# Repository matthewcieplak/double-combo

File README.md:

# AmpSim

## Author

Extralife Instruments

## Description

Amp sim module for Eurorack using Daisy Patch.

## Programming setup: 

Plug the daisy patch into the PC using USB.

Download and install Zadig. Run it to install the USB driver.

Build and program the device from source in VS code or use the daisy web uploader.

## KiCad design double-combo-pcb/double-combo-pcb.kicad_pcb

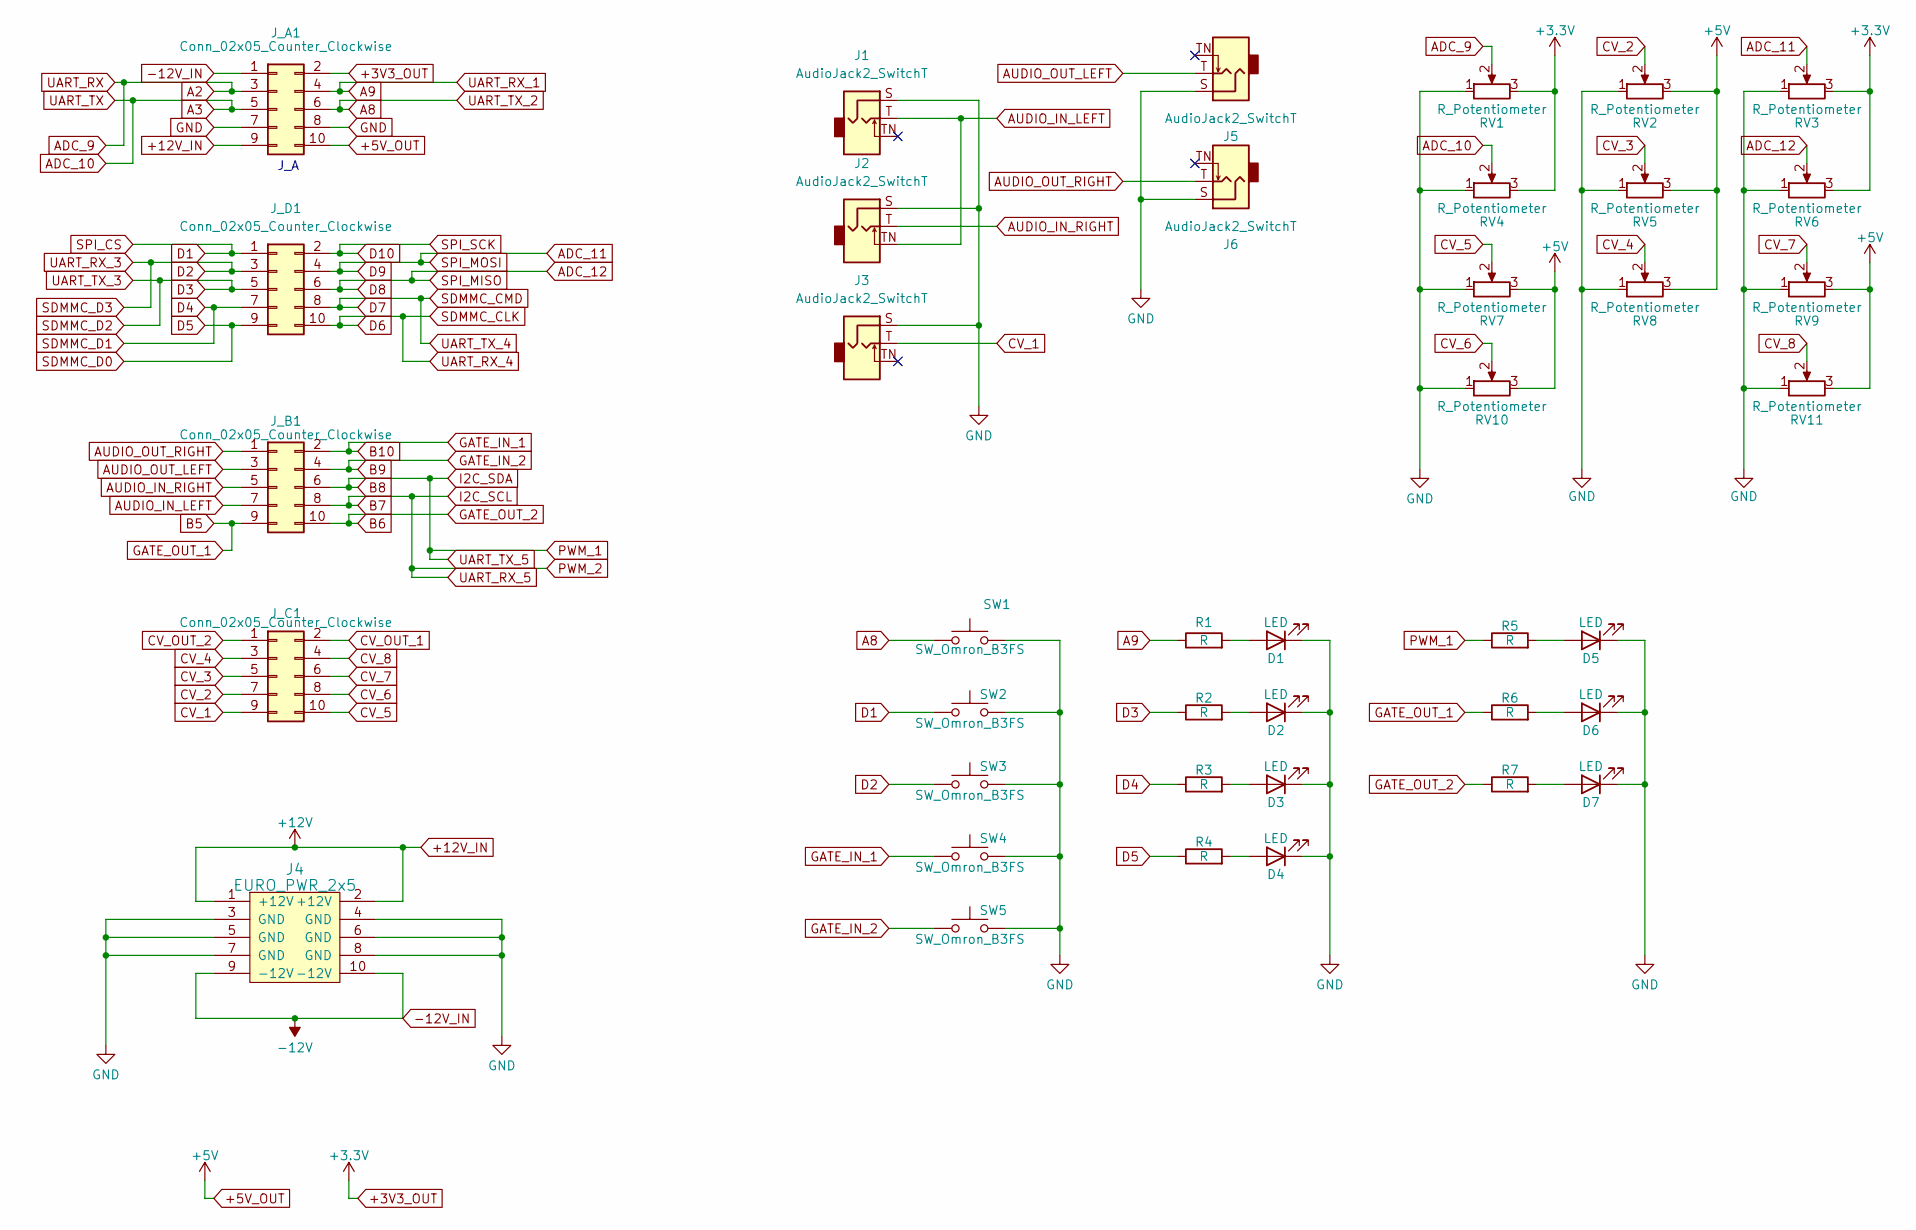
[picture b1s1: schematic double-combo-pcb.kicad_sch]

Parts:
D1, D2, D3, D4, D5, D6, D7: LED; LED_D3.0mm
J1, J2, J3, J5, J6: AudioJack2_SwitchT; Jack_3.5mm_QingPu_WQP-PJ398SM_Vertical_CircularHoles
J4: EURO_PWR_2x5; PinHeader_2x05_P2.54mm_Vertical
J_A1: Conn_02x05_Counter_Clockwise; PinSocket_2x05_P2.54mm_Vertical
J_B1: Conn_02x05_Counter_Clockwise; PinSocket_2x05_P2.54mm_Vertical
J_C1: Conn_02x05_Counter_Clockwise; PinSocket_2x05_P2.54mm_Vertical
J_D1: Conn_02x05_Counter_Clockwise; PinSocket_2x05_P2.54mm_Vertical
R1, R2, R3, R4, R5, R6, R7: R; R_Axial_DIN0411_L9.9mm_D3.6mm_P15.24mm_Horizontal
RV1, RV2, RV3, RV4, RV5, RV6, RV7, RV8, RV9, RV10, RV11: R_Potentiometer; Potentiometer_Alpha_RD901F-40-00D_Single_Vertical_CircularH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
SW1, SW2, SW3, SW4, SW5: SW_Omron_B3FS; SW_TH_Tactile_Omron_B3F-10xx

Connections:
+3V3_OUT: J_A1.2, RV1.3, RV3.3, RV4.3, RV6.3
+5V_OUT: J_A1.10, RV2.3, RV5.3, RV7.3, RV8.3, RV9.3, RV10.3, RV11.3
+12V_IN: J4.1 (+12V), J4.2 (+12V), J_A1.9
-12V_IN: J4.9 (-12V), J4.10 (-12V), J_A1.1
A2: J_A1.3, RV1.2
A3: J_A1.5, RV4.2
A8: J_A1.6, SW1.1
A9: J_A1.4, R1.1
ADC_11: J_D1.4, RV3.2
ADC_12: J_D1.6, RV6.2
AUDIO_IN_LEFT: J1.T, J2.TN, J_B1.7
AUDIO_IN_RIGHT: J2.T, J_B1.5
AUDIO_OUT_LEFT: J5.T, J_B1.3
AUDIO_OUT_RIGHT: J6.T, J_B1.1
B5: J_B1.9, R6.1
B6: J_B1.10, R7.1
B7: J_B1.8
B8: J_B1.6, R5.1
B9: J_B1.4, SW5.1
B10: J_B1.2, SW4.1
CV_1: J3.T, J_C1.9
CV_2: J_C1.7, RV2.2
CV_3: J_C1.5, RV5.2
CV_4: J_C1.3, RV8.2
CV_5: J_C1.10, RV7.2
CV_6: J_C1.8, RV10.2
CV_7: J_C1.6, RV9.2
CV_8: J_C1.4, RV11.2
CV_OUT_1: J_C1.2
CV_OUT_2: J_C1.1
D1: J_D1.1, SW2.1
D2: J_D1.3, SW3.1
D3: J_D1.5, R2.1
D4: J_D1.7, R3.1
D5: J_D1.9, R4.1
D6: J_D1.10
D7: J_D1.8
D10: J_D1.2
GND: D1.1 (K), D2.1 (K), D3.1 (K), D4.1 (K), D5.1 (K), D6.1 (K), D7.1 (K), J1.S, J2.S, J3.S, J4.3 (GND), J4.4 (GND), J4.5 (GND), J4.6 (GND), J4.7 (GND), J4.8 (GND), J5.S, J6.S, J_A1.7, J_A1.8, RV1.1, RV2.1, RV3.1, RV4.1, RV5.1, RV6.1, RV7.1, RV8.1, RV9.1, RV10.1, RV11.1, SW1.2, SW2.2, SW3.2, SW4.2, SW5.2
unnamed: D1.2 (A), R1.2
unnamed: D2.2 (A), R2.2
unnamed: D3.2 (A), R3.2
unnamed: D4.2 (A), R4.2
unnamed: D5.2 (A), R5.2
unnamed: D6.2 (A), R6.2
unnamed: D7.2 (A), R7.2

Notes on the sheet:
J_A

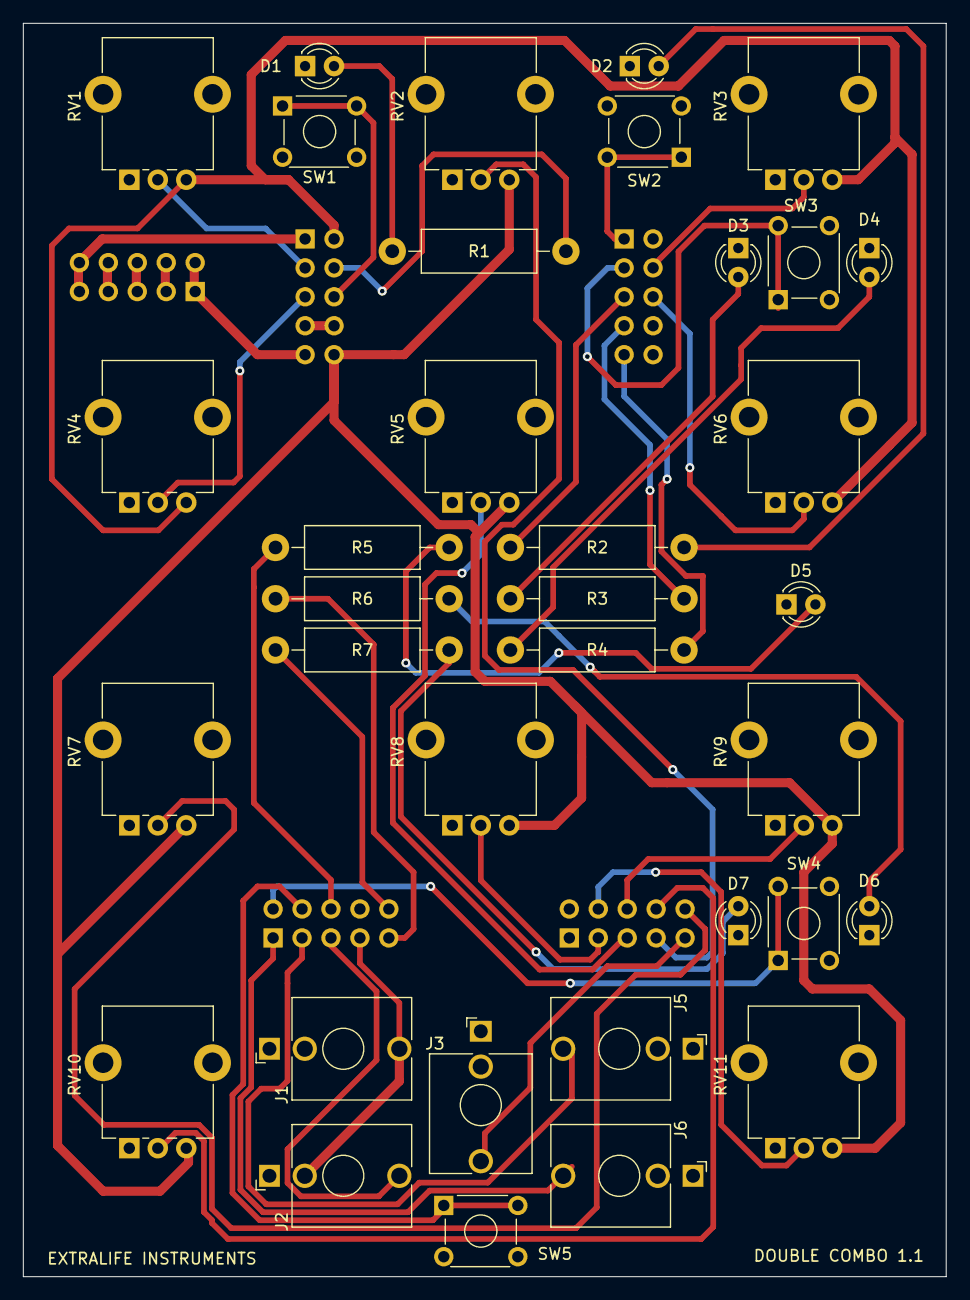
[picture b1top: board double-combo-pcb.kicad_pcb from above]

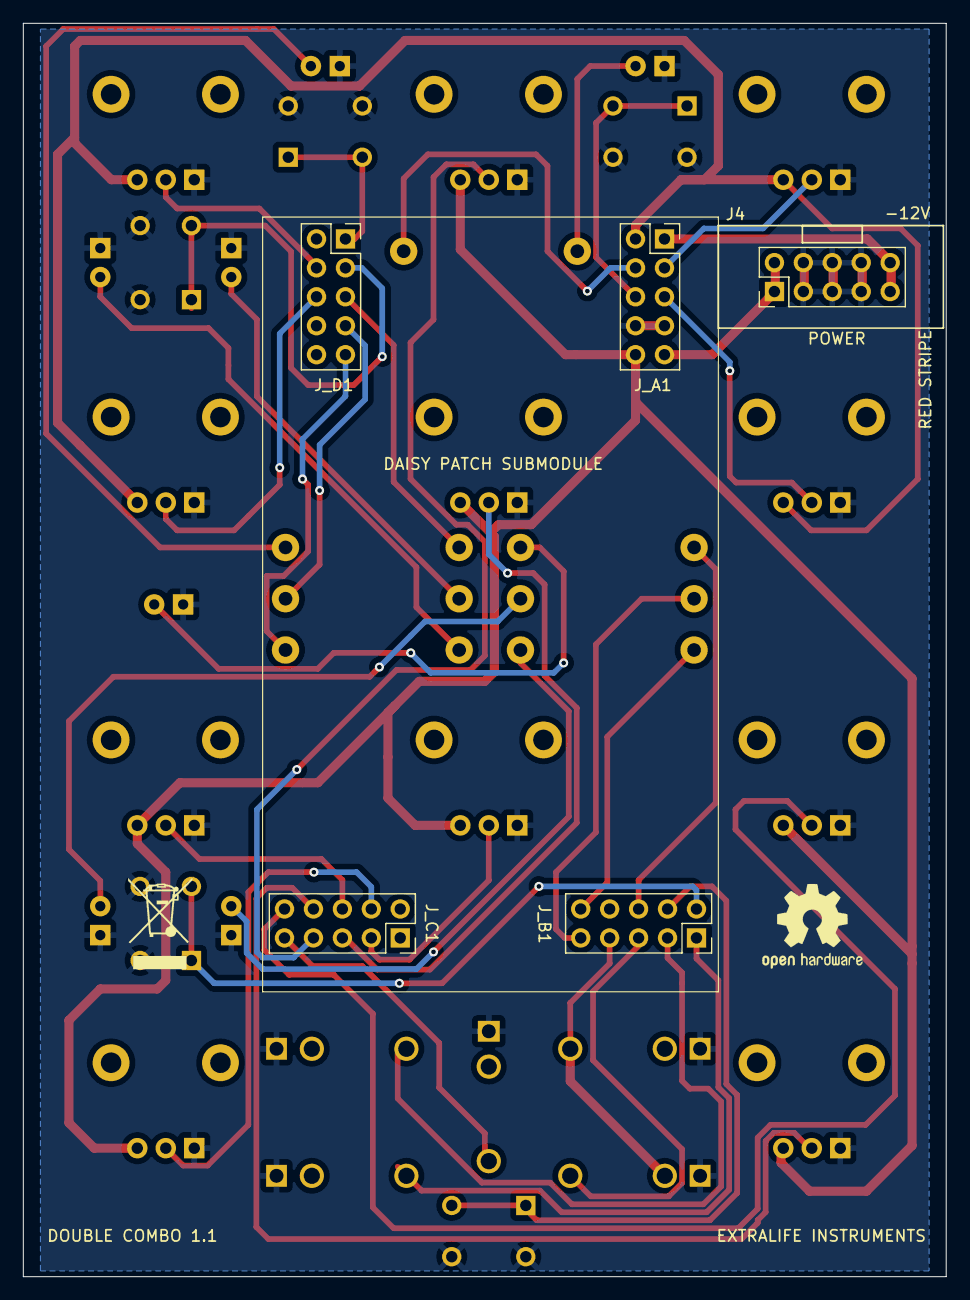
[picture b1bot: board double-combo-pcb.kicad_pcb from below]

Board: 2 copper layers, 81.0 x 110.0 mm, 40 parts (5 on the bottom side), 40 nets.

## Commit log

2025-04-13 Adding KiCad files
2025-04-13 Adding front panel graphics
2025-04-13 Adding delay FX
2025-04-13 Refactoring signal processing
2025-04-13 fix: correcting delay feedback logic
